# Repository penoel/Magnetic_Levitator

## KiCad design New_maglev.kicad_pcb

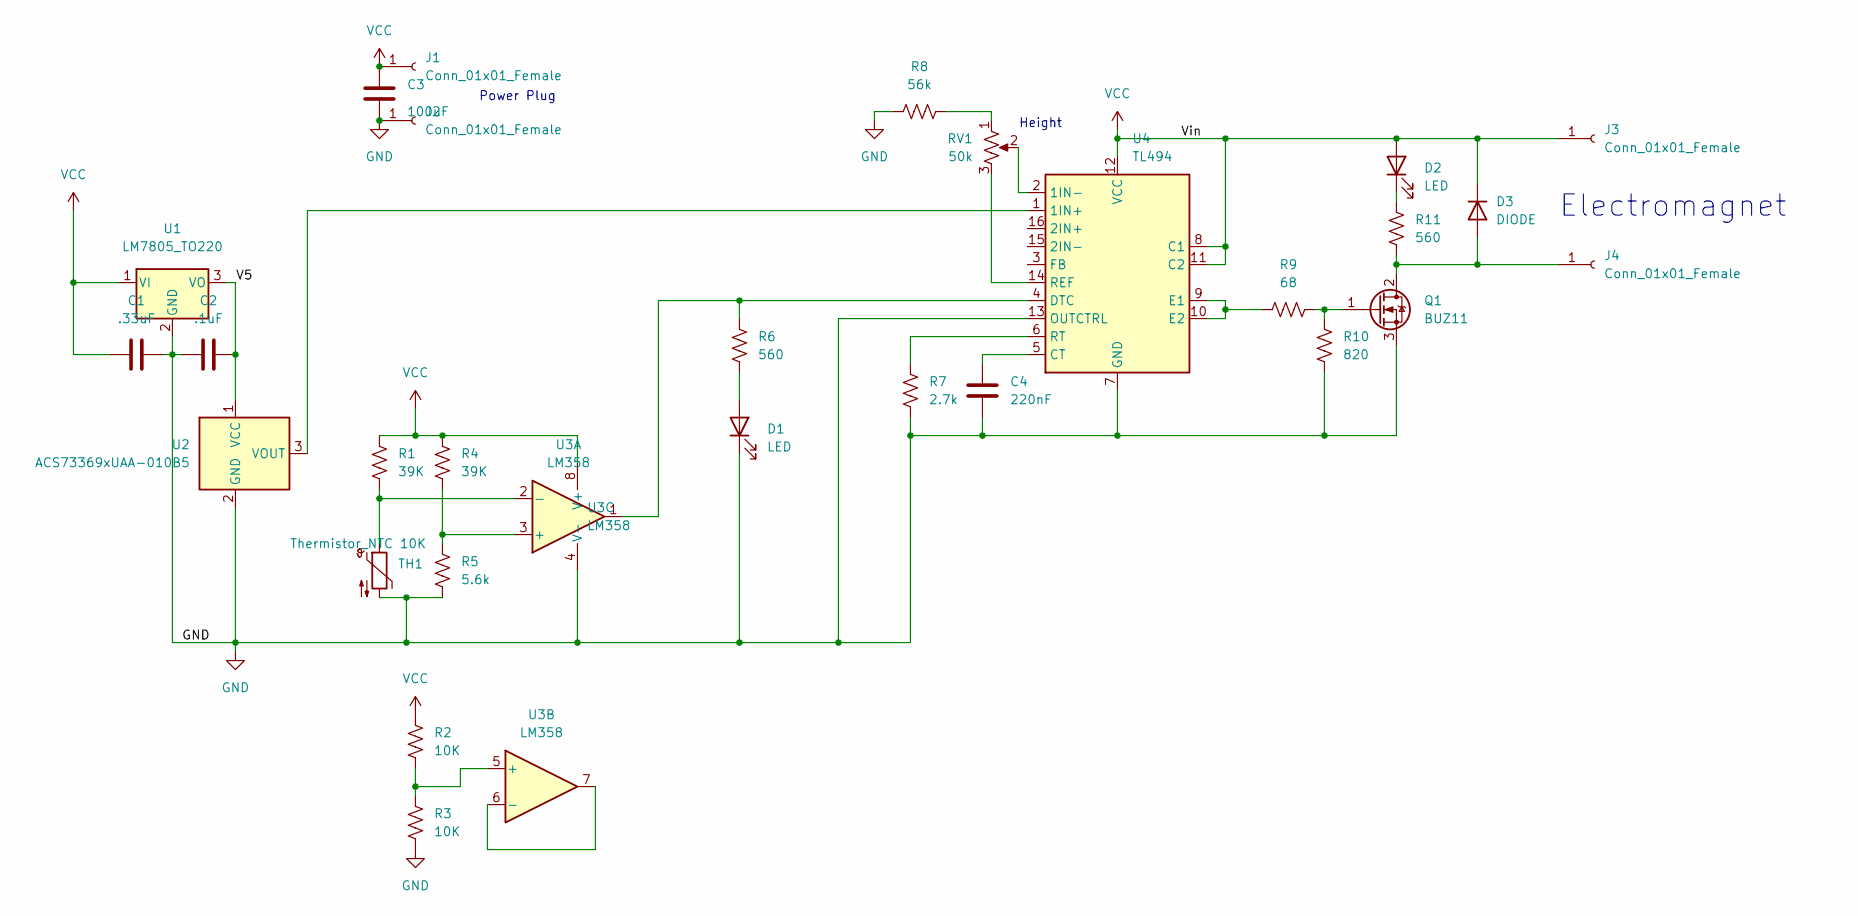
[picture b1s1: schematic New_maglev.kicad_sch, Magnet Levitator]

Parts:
C1: .33uF; C_Disc_D4.7mm_W2.5mm_P5.00mm
C2: .1uF; C_Disc_D4.7mm_W2.5mm_P5.00mm
C3: 100uF; CP_Radial_D10.0mm_P5.00mm
C4: 220nF; C_Disc_D4.7mm_W2.5mm_P5.00mm
D1, D2: LED; LED_D5.0mm
D3: DIODE; D_DO-41_SOD81_P10.16mm_Horizontal
J1, J2: Conn_01x01_Female; Test_Point_2.67x1.02mm
J3, J4: Conn_01x01_Female; PinHeader_1x01_P1.00mm_Vertical
Q1: BUZ11; TO-220-3_Vertical
R1, R4: 39K; R_Axial_DIN0207_L6.3mm_D2.5mm_P10.16mm_Horizontal
R2, R3: 10K; R_Axial_DIN0207_L6.3mm_D2.5mm_P10.16mm_Horizontal
R5: 5.6k; R_Axial_DIN0207_L6.3mm_D2.5mm_P10.16mm_Horizontal
R6, R11: 560; R_Axial_DIN0207_L6.3mm_D2.5mm_P10.16mm_Horizontal
R7: 2.7k; R_Axial_DIN0207_L6.3mm_D2.5mm_P10.16mm_Horizontal
R8: 56k; R_Axial_DIN0207_L6.3mm_D2.5mm_P10.16mm_Horizontal
R9: 68; R_Axial_DIN0207_L6.3mm_D2.5mm_P10.16mm_Horizontal
R10: 820; R_Axial_DIN0207_L6.3mm_D2.5mm_P10.16mm_Horizontal
RV1: 50k; Potentiometer_ACP_CA9-H5_Horizontal
TH1: Thermistor_NTC 10K; PinHeader_1x02_P2.54mm_Vertical
U1: LM7805_TO220; TO-220-3_Vertical
U2: ACS73369xUAA-010B5; Allegro_SIP-3
U3: LM358; DIP-8_W7.62mm
U4: TL494; DIP-16_W7.62mm

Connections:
/V5: C2.2, U1.3 (VO), U2.1 (VCC)
GND: C1.2, C2.1, C3.2, C4.2, D1.1 (K), J2.1, Q1.3 (S), R3.2, R5.2, R7.2, R8.1, R10.2, TH1.2, U1.2 (GND), U2.2 (GND), U3.4 (V-), U4.7 (GND), U4.13 (OUTCTRL)
unnamed: C4.1, U4.5 (CT)
unnamed: D1.2 (A), R6.2
unnamed: D2.1 (K), R11.1
unnamed: D3.2 (A), J4.1, Q1.2 (D), R11.2
unnamed: Q1.1 (G), R9.2, R10.1
unnamed: R1.2, TH1.1, U3.2 (-)
unnamed: R2.2, R3.1, U3.5 (+)
unnamed: R4.2, R5.1, U3.3 (+)
unnamed: R6.1, U3.1, U4.4 (DTC)
unnamed: R7.1, U4.6 (RT)
unnamed: R8.2, RV1.1
unnamed: R9.1, U4.9 (E1), U4.10 (E2)
unnamed: RV1.2, U4.2 (1IN-)
unnamed: RV1.3, U4.14 (REF)
unnamed: U2.3 (VOUT), U4.1 (1IN+)
unnamed: U3.6 (-), U3.7
VCC: C1.1, C3.1, D2.2 (A), D3.1 (K), J1.1, J3.1, R1.1, R2.1, R4.1, U1.1 (VI), U3.8 (V+), U4.8 (C1), U4.11 (C2), U4.12 (VCC)

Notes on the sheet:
Height
Electromagnet
Power Plug

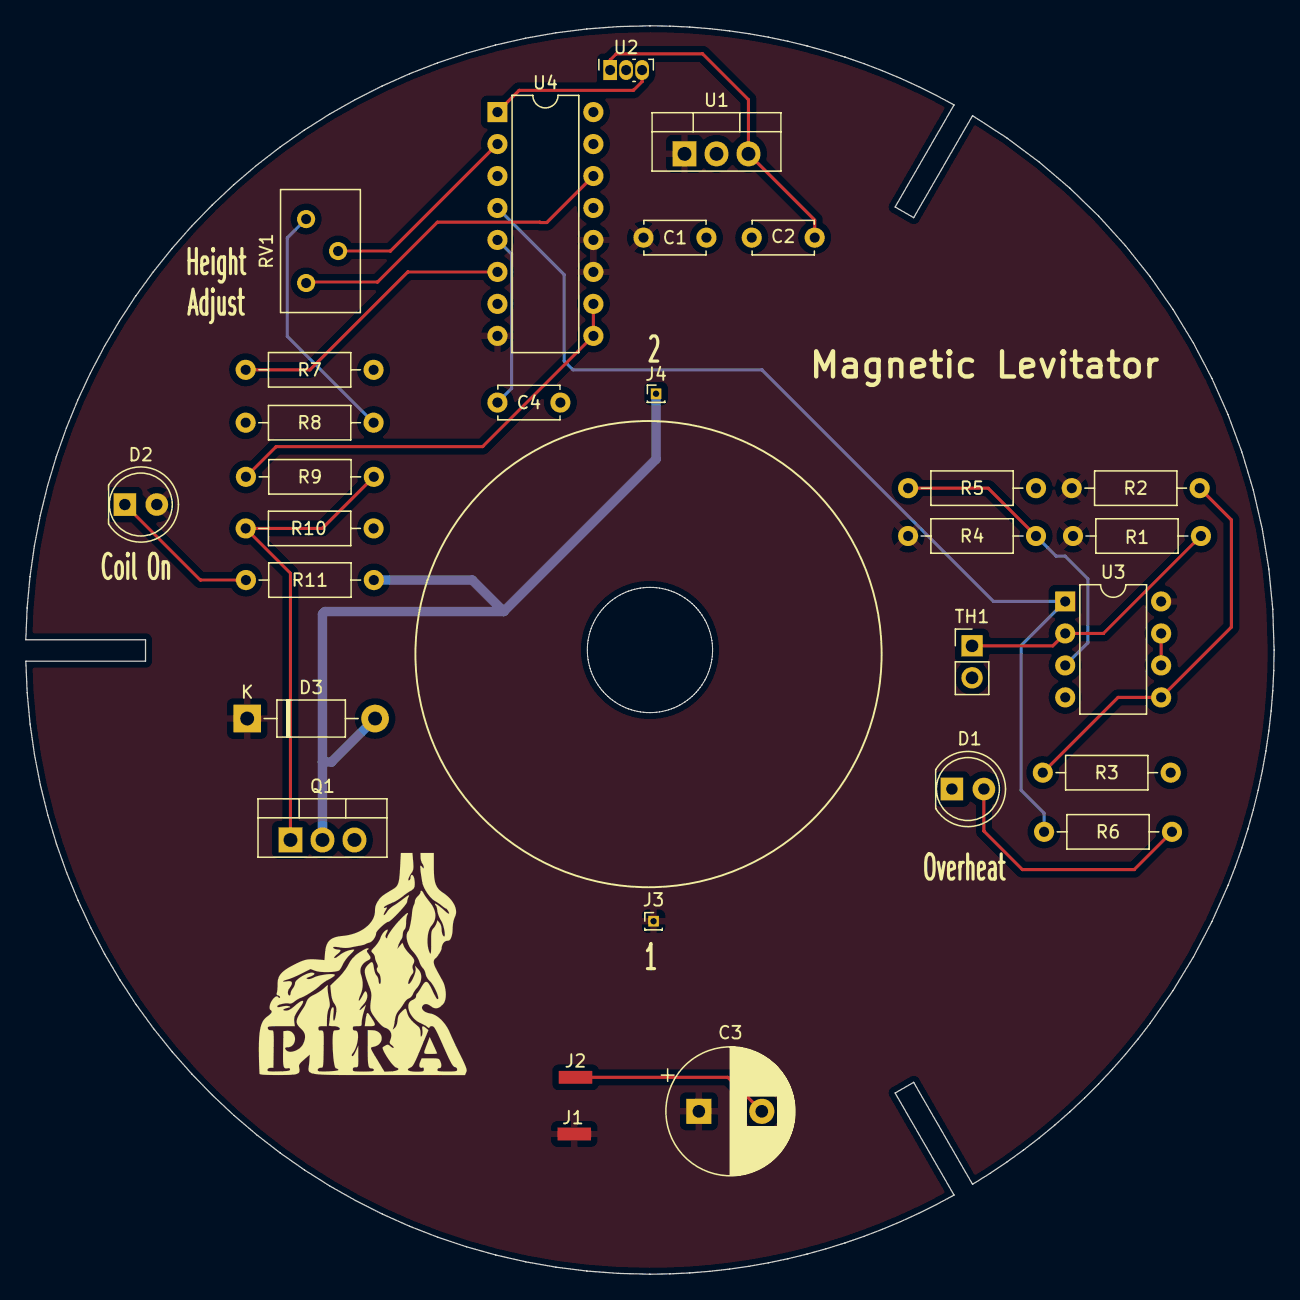
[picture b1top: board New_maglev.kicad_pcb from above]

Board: 2 copper layers, 99.2 x 99.2 mm, 29 parts (0 on the bottom side), 19 nets.
